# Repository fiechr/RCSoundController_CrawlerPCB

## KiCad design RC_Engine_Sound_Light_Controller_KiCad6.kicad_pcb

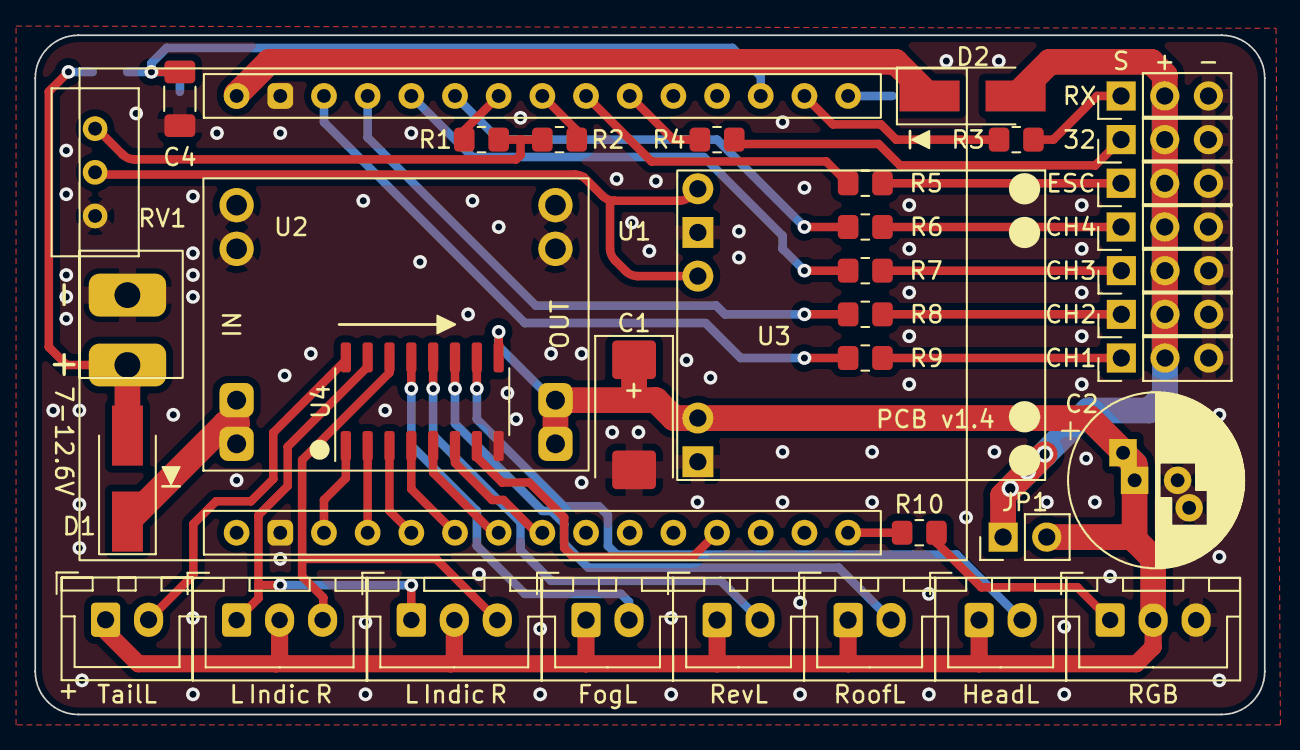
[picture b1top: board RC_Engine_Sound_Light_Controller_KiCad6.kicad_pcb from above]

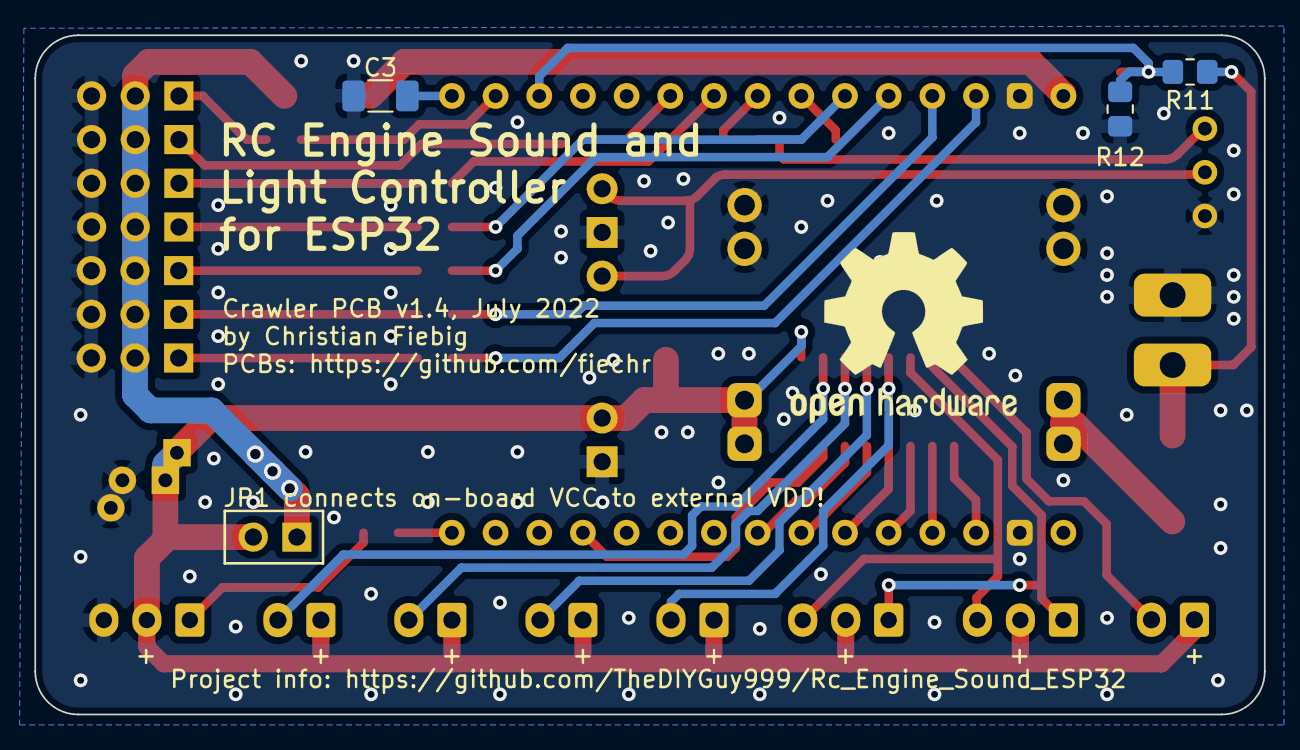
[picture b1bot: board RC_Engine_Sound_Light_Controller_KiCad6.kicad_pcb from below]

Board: 2 copper layers, 71.5 x 39.5 mm, 40 parts (3 on the bottom side), 42 nets.

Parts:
C1: 330µF; CP_EIA-7343-30_AVX-N_Pad2.25x2.55mm_HandSolder
C2: 1mF; CP_Radial_D10.0mm_P2.50mm_P5.00mm
C3: 4.7µF; C_1206_3216Metric_Pad1.33x1.80mm_HandSolder
C4: 100nF; C_1206_3216Metric_Pad1.33x1.80mm_HandSolder
D1: Battery Polarity Protection; D_SMA_Handsoldering
D2: USB Supply Protection; D_SMA_Handsoldering
J1: RX; PinHeader_1x03_P2.54mm_Vertical
J2: HeadL; JST_XH_B2B-XH-A_1x02_P2.50mm_Vertical
J3: TailL; JST_XH_B2B-XH-A_1x02_P2.50mm_Vertical
J4: RoofL; JST_XH_B2B-XH-A_1x02_P2.50mm_Vertical
J5: RevL; JST_XH_B2B-XH-A_1x02_P2.50mm_Vertical
J6, J7: Indic; JST_XH_B3B-XH-A_1x03_P2.50mm_Vertical
J8: Battery input; InputPowerSolderPads
J9: FogL; JST_XH_B2B-XH-A_1x02_P2.50mm_Vertical
J10: RGB; JST_XH_B3B-XH-A_1x03_P2.50mm_Vertical
J11: 32; PinHeader_1x03_P2.54mm_Vertical
J12: CH1; PinHeader_1x03_P2.54mm_Vertical
J13: CH2; PinHeader_1x03_P2.54mm_Vertical
J14: CH3; PinHeader_1x03_P2.54mm_Vertical
J15: ESC; PinHeader_1x03_P2.54mm_Vertical
J16: CH4; PinHeader_1x03_P2.54mm_Vertical
JP1: VCC VDD Bridge; PinHeader_1x02_P2.54mm_Vertical
R1, R2: 10kΩ; R_0805_2012Metric_Pad1.20x1.40mm_HandSolder
R3, R5, R6, R7, R8, R9: 330Ω; R_0805_2012Metric_Pad1.20x1.40mm_HandSolder
R4: 180Ω; R_0805_2012Metric_Pad1.20x1.40mm_HandSolder
R10: 100Ω; R_0805_2012Metric_Pad1.20x1.40mm_HandSolder
R11: 22kΩ; R_0805_2012Metric_Pad1.20x1.40mm_HandSolder
R12: 100kΩ; R_0805_2012Metric_Pad1.20x1.40mm_HandSolder
RV1: 20kΩ; Potentiometer_Bourns_3296W_Vertical
U1: ESP32_DEVKITV1_30PIN
U2: MP1584EN_BreakoutBoard
U3: PAM8403_BreakoutBoard; PAM8403_NOSPEAKER_BreakoutBoard
U4: ULN2003; SO-16_3.9x9.9mm_P1.27mm

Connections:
+BATT: D1.2 (A), J8.1, R11.1
-BATT: C1.2, C2.2, C3.2, C4.2, J1.3, J8.2, J10.3, J11.3, J12.3, J13.3, J14.3, J15.3, J16.3, R12.2, RV1.3, U1.2 (GND), U1.29 (GND), U2.1 (GND), U2.4 (GND), U2.5 (GND), U2.8 (GND), U3.2 (AGND), U3.5 (GND), U4.8 (GND)
/AUDIO_INPUT: RV1.2, U3.1 (INL), U3.3 (INR)
/AUDIO_JOINT: R1.2, R2.2, RV1.1
/BATT_VIN: D1.1 (K), U2.2 (VIN), U2.6 (VIN)
/CH1: J12.1, R9.2
/CH2: J13.1, R8.2
/CH3: J14.1, R7.2
/CH4: J16.1, R6.2
/EN_PIN: C3.1, U1.16 (EN)
/ESC: J15.1, R5.2
/PIN_32: J11.1, R4.2
/RGB: J10.1, R10.2
/RX: J1.1, R3.2
/VDD_VIN: D2.1 (K), U1.30 (VIN)
D2: U1.4 (D2), U4.2 (I2)
D3: U1.12 (D3), U4.7 (I7)
D4: U1.5 (D4), U4.3 (I3)
D5: U1.8 (D5), U4.6 (I6)
D12: R8.1, U1.27 (D12)
D13: R9.1, U1.28 (D13)
D14: R7.1, U1.26 (D14)
D15: U1.3 (D15), U4.1 (I1)
D16: U1.6 (D16), U4.4 (I4)
D17: U1.7 (D17), U4.5 (I5)
D23: R10.1, U1.15 (D23)
D25: R1.1, U1.23 (D25)
D26: R2.1, U1.24 (D26)
D27: R6.1, U1.25 (D27)
D32: R4.1, U1.21 (D32)
D33: R5.1, U1.22 (D33)
D36: R3.1, U1.17 (D36)
D39: C4.1, R11.2, R12.1, U1.18 (D39)
FOGLIGHTS: J9.2, U4.13 (O4)
HEADLIGHTS: J2.2, U4.10 (O7)
INDICATOR_L: J6.1, J7.1, U4.15 (O2)
INDICATOR_R: J6.3, J7.3, U4.14 (O3)
REVERSING: J5.2, U4.12 (O5)
ROOFLIGHTS: J4.2, U4.11 (O6)
TAILLIGHTS: J3.2, U4.16 (O1)
VCC: C1.1, C2.1, J2.1, J3.1, J4.1, J5.1, J6.2, J7.2, J9.1, J10.2, JP1.2 (B), U2.3 (VOUT), U2.7 (VOUT), U3.4 (VCC), U4.9 (COM)
VDD: D2.2 (A), J1.2, J11.2, J12.2, J13.2, J14.2, J15.2, J16.2, JP1.1 (A)

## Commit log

2022-05-17 Initial commit.
2022-05-17 Added RZ7886 to schematic
2022-05-20 All but data lines routed
2022-05-21 Minor corrections.
2022-05-21 Pins 32 and 33 connected to driver IC.
2022-05-22 Added seconds tantal cap.
2022-05-22 Added VDD diode.
2022-05-23 Removed ESC and Pin 32 headers.
2022-05-23 Removed EN cap, added USB diode.
2022-05-23 Rounded corners.
2022-05-24 Added voltage divider for battery voltage measurement. Renamed power nets.
2022-05-24 Changed +5V to VCC.
2022-06-07 Minor silkscreen improvements.
2022-06-08 Moved pot slightly to the left.
2022-06-08 Some minor changes.
2022-06-10 Corrected 5V caps silkscreen polarization.
2022-06-10 Added battery voltage measurement divider, cap and (re-added) EN cap on the backside (optional).
2022-06-15 Moved input capacitor 1 mm up and away from USB port.
2022-06-16 Completed voltage divider.
2022-06-18 Minor changes.
2022-07-05 Added solder jumper between VCC and VDD.
2022-07-06 Fixed wrong headlight pin (moved from D18 to D3).
2022-07-06 C2 pad traces on front and back.
2022-07-06 Minor changes to C2 pads.
2022-07-07 Audio traces optimized.
2022-07-07 Audio traces optimized. Added small ceramic capacitor at driver IC.
2022-07-07 Solid GND pad for darlington array IC.
2022-07-08 JLCPCB v1.3 order
2022-07-08 Added dot for pin #1 for darlington array IC.
2022-07-08 Added GND via between RX line and pins.
2022-07-16 Changed to v1.4, added track for headers and cap on both sides of VCC/VDD.
2022-07-16 Double tracks for VDD headers and big caps. Reduced size of tracks connecting to caps and driver IC.
2022-07-17 Added more information on the backside.
2022-07-31 Added larger vias for VCC to VDD connection.
